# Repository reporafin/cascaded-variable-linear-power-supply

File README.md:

# Cascaded Multi-Rail AC-DC Linear Power Supply

A hardware design and simulation repository for a custom variable linear AC-to-DC power supply. The circuit relies on the LM adjustable voltage regulator and the fixed voltage regulators to provide stable, clean power for lab and prototyping environments. 

## Features
* **Multi-Rail Output:** Provides four distinct power rails: an adjustable output (1.25V–21V) via an LM317, and three fixed digital logic rails (12V, 5V, 3.3V).
* **Cascaded Architecture:** The fixed voltage regulators (LM7812, LM7805, and a LM-1117) are strategically cascaded. The main 34V DC bus feeds the 12V IC, which feeds the 5V IC, which finally feeds the LM1117-3.3 LDO to provide a clean 3.3V logic rail. This distributes thermal dissipation across the board and prevents the lower-voltage ICs from instantly overheating.
* **Thermal & Layout Optimization:** Designed on a strictly single-layer PCB using a manual 1.0mm common ground bus to safely manage continuous current and heat.
* **Safety & Transient Protection:** Integrated 1N4007 flywheel (flyback) diodes in reverse-biased parallel across the LM317 and LM7812 regulators. This creates a safe discharge path for output capacitors and protects the silicon from reverse-current spikes during power-off events.
* **Validated Design:** Component tolerances, inductive flyback protection, and ripple voltages across the cascaded rails were verified in LTspice prior to physical layout.

## Repository Structure

```text
├── simulation/  # LTspice simulation files and waveform plots
├── hardware/    # KiCad schematics, PCB layout, and 3D models
│   └── gerbers/ # Manufacturing files for PCB fabrication
├── hardware_1.2/ # New KiCad schematics, PCB layout, and 3D models with some minor changes
│   └── gerbers/ # Manufacturing files for New PCB fabrication
└── README.md
```

## Prerequisites

To view or modify the files in this project, you will need:
* **[LTspice](https://www.analog.com/en/design-center/design-tools-and-calculators/ltspice-simulator.html):** For running the `.asc` circuit simulations.
* **[KiCad (v7.0+)](https://www.kicad.org/):** For opening the schematic and PCB files.

## Getting Started

1. **Simulation:** Open `Simulation/main_design.asc` in LTspice and click 'Run' to view the transient analysis and ripple voltages.
2. **Hardware:** Open `Hardware_1.2/vdc.kicad_pro` in KiCad to explore the schematic and PCB layout.
3. **Fabrication:** The production-ready Gerber files are located in `hardware/gerbers/`.

## License
This project is open-source and available under the [MIT License](LICENSE).

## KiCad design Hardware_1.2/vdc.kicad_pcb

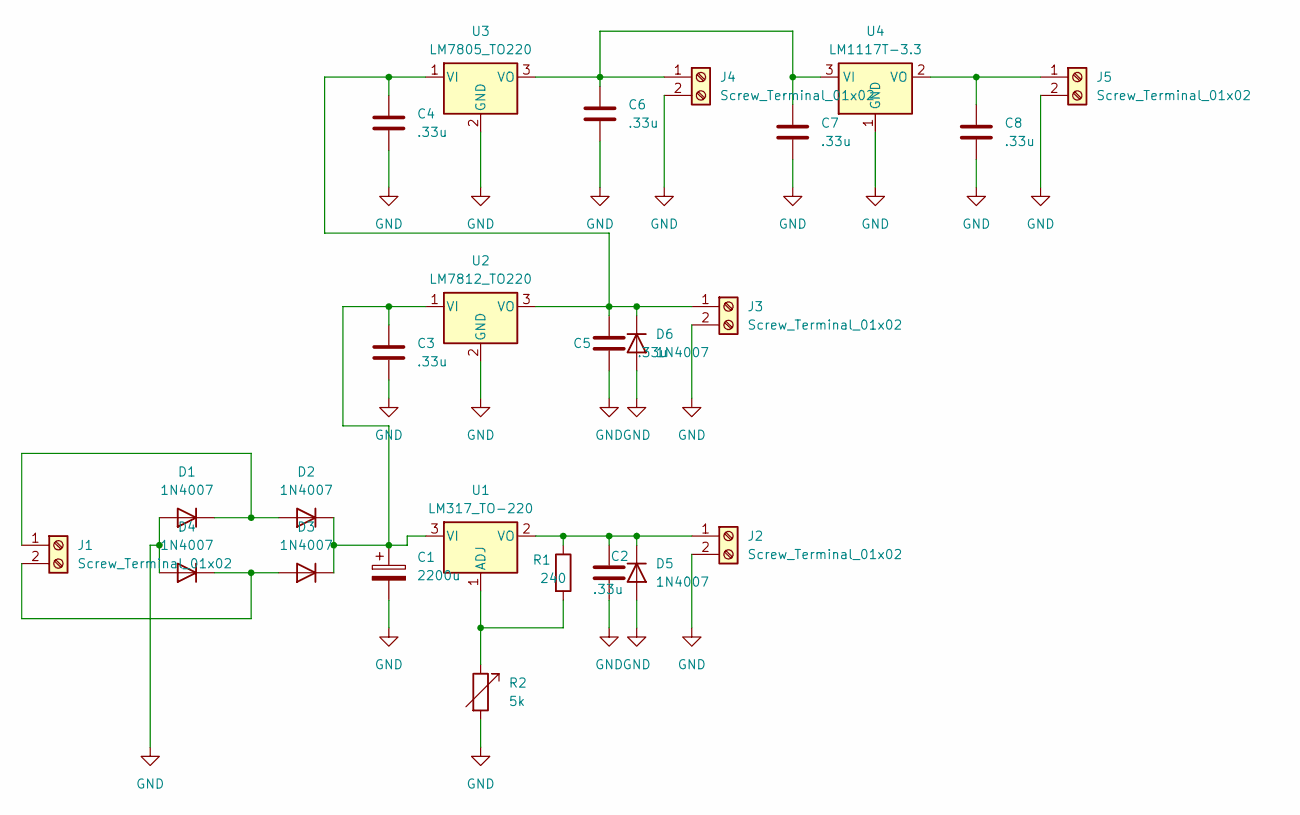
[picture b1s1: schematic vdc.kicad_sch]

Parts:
C1: 2200u; CP_Radial_D16.0mm_P7.50mm
C2, C3, C4, C5, C6, C7, C8: .33u; C_Disc_D5.0mm_W2.5mm_P5.00mm
D1, D2, D3, D4, D5, D6: 1N4007; D_DO-41_SOD81_P10.16mm_Horizontal
J1, J2, J3, J4, J5: Screw_Terminal_01x02; TerminalBlock_Phoenix_MKDS-1,5-2-5.08_1x02_P5.08mm_Horizont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
R1: 240; R_Axial_DIN0614_L14.3mm_D5.7mm_P25.40mm_Horizontal
R2: 5k; Potentiometer_Bourns_3386P_Vertical
U1: LM317_TO-220; TO-220-3_Vertical
U2: LM7812_TO220; TO-220-3_Vertical
U3: LM7805_TO220; TO-220-3_Vertical
U4: LM1117T-3.3; TO-220-3_Vertical

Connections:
GND: C1.2, C2.2, C3.2, C4.2, C5.2, C6.2, C7.2, C8.2, D1.2 (A), D4.2 (A), D5.2 (A), D6.2 (A), J2.2, J3.2, J4.2, J5.2, R2.2, U2.2 (GND), U3.2 (GND), U4.1 (GND)
unnamed: D1.1 (K), D2.2 (A), J1.1
unnamed: C1.1, C3.1, D2.1 (K), D3.1 (K), U1.3 (VI), U2.1 (VI)
unnamed: D3.2 (A), D4.1 (K), J1.2
unnamed: C2.1, D5.1 (K), J2.1, R1.1, U1.2 (VO)
unnamed: C4.1, C5.1, D6.1 (K), J3.1, U2.3 (VO), U3.1 (VI)
unnamed: C6.1, C7.1, J4.1, U3.3 (VO), U4.3 (VI)
unnamed: C8.1, J5.1, U4.2 (VO)
unnamed: R1.2, R2.1, U1.1 (ADJ)

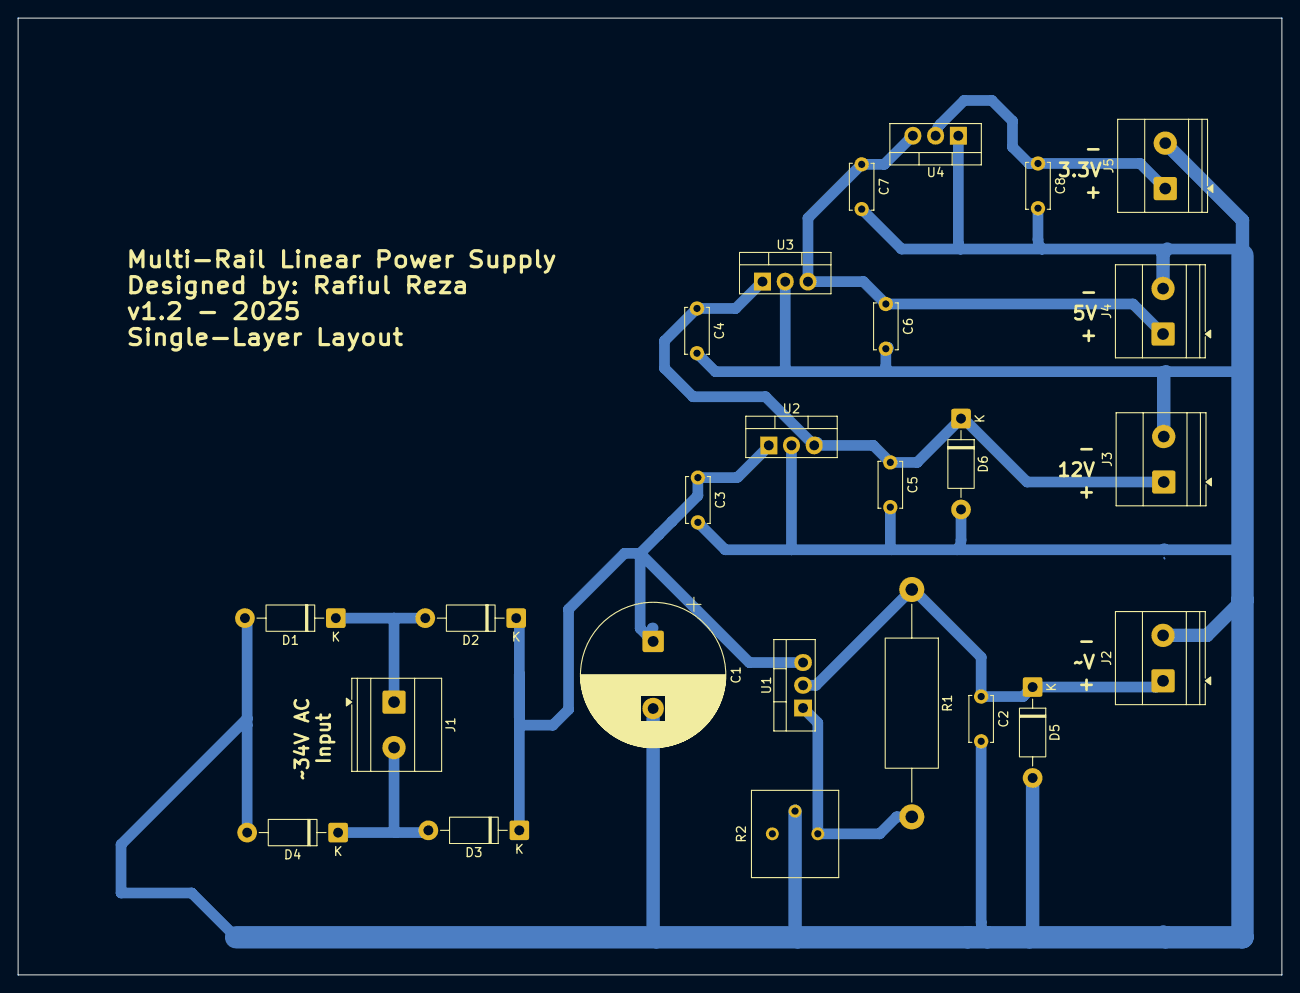
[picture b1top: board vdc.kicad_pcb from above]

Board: 2 copper layers, 141.2 x 106.9 mm, 25 parts (0 on the bottom side), 9 nets.
